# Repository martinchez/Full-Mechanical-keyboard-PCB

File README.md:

# Custom Mechanical Keyboard PCB Design

This repository contains the design files and resources for a custom mechanical keyboard PCB created using KiCad. The project includes schematics, PCB layout, and production files, aiming to make a fully functional and customizable mechanical keyboard.

## Project Overview

This keyboard design project includes:
- **Schematic Design**: Detailed layout of switches, diodes, and controller connections.
- **PCB Layout**: A compact and optimized PCB design suitable for mechanical switches.
- **Production Files**: Ready-to-use Gerber files and a BOM (Bill of Materials) for ordering components.

## Features

- **Hot-swappable Switches** (optional): Easy switch customization without soldering.
- **RGB Backlighting** (optional): Support for individually addressable RGB LEDs.
- **USB-C Interface**: Modern connectivity option.
- **Customizable Firmware**: Compatible with QMK or VIA for programmable key layouts.

## Folder Structure

- `schematics/`: KiCad schematic files for the keyboard circuit.
- `pcb_layout/`: KiCad PCB layout files with switch, diode, and microcontroller placements.
- `gerber_files/`: Gerber files for PCB manufacturing.
- `bom/`: Bill of Materials for sourcing components.

## Getting Started

1. Clone the repository:
   ```bash
   git clone 
   cd 
Open the project in KiCad by loading the .kicad_pro file in the root directory.

Make any modifications needed to suit your preferred keyboard layout.

## Usage
Editing the Schematic
Open the `schematics/` folder and modify connections or components as needed.

# PCB Layout
The `pcb_layout/` folder contains the PCB layout file, where you can make adjustments to the component placements or routing.

# Generating Gerber Files
After making changes, you can generate new Gerber files by:

1. Opening the PCB Editor in KiCad.
2. Going to File > Plot to export your Gerber files into the `gerber_files/` folder.

## License
This project is licensed under the MIT License

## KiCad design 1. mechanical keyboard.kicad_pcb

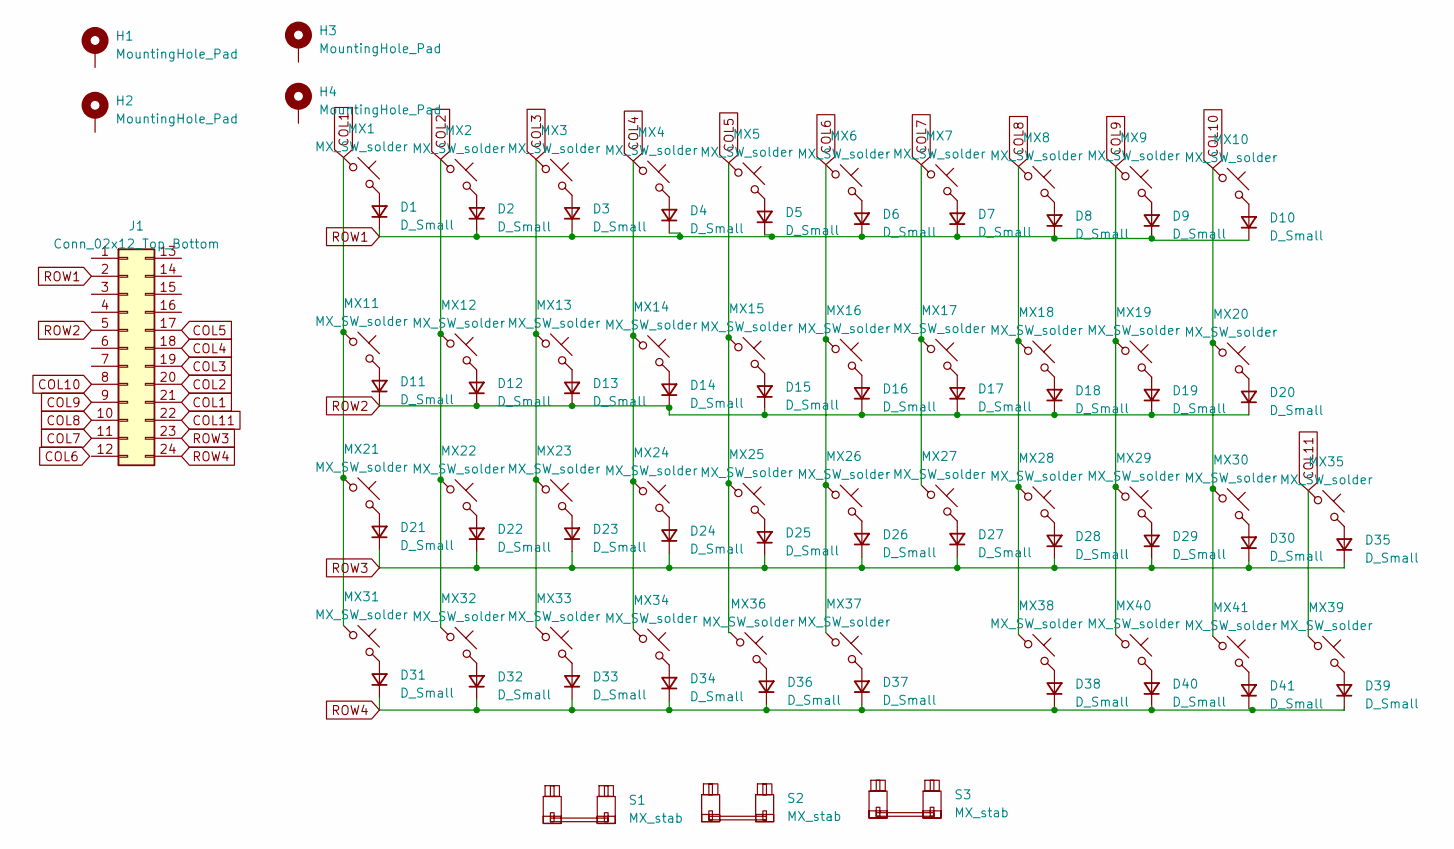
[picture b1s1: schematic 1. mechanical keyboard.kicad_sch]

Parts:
D1, D2, D3, D4, D5, D6, D7, D8, D9, D10, D11, D12, D13, D14, D15, D16, D17, D18, D19, D20, D21, D22, D23, D24, D25, D26, D27, D28, D29, D30, D31, D32, D33, D34, D35, D36, D37, D38, D39, D40, D41: D_Small; D_SOD-123
H1, H2, H3, H4: MountingHole_Pad; MountingHole_2.7mm_M2.5_Pad_Via
J1: Conn_02x12_Top_Bottom; ProMicro_Reversible_Single
MX1, MX2, MX3, MX4, MX5, MX6, MX7, MX8, MX9, MX12, MX13, MX14, MX15, MX16, MX17, MX18, MX19, MX22, MX23, MX24, MX25, MX26, MX27, MX28, MX29, MX30, MX32, MX33, MX34, MX35, MX36, MX37, MX38, MX39, MX40: MX_SW_solder; SW_MX_1u
MX10, MX21: MX_SW_solder; SW_MX_1.75u
MX11, MX31, MX41: MX_SW_solder; SW_MX_1.25u
MX20: MX_SW_solder; SW_MX_1.5u
S1: MX_stab; STAB_MX_P_2u
S2: MX_stab; STAB_MX_P_2.25u
S3: MX_stab; STAB_MX_P_6.25u

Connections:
COL1: J1.21, MX1.1, MX11.1, MX21.1, MX31.1
COL2: J1.20, MX2.1, MX12.1, MX22.1, MX32.1
COL3: J1.19, MX3.1, MX13.1, MX23.1, MX33.1
COL4: J1.18, MX4.1, MX14.1, MX24.1, MX34.1
COL5: J1.17, MX5.1, MX15.1, MX25.1, MX36.1
COL6: MX6.1, MX16.1, MX26.1, MX37.1
COL7: J1.11, MX7.1, MX17.1, MX27.1
COL8: J1.10, MX8.1, MX18.1, MX28.1, MX38.1
COL9: J1.9, MX9.1, MX19.1, MX29.1, MX40.1
COL10: J1.8, MX10.1, MX20.1, MX30.1, MX41.1
COL11: J1.22, MX35.1, MX39.1
unnamed: D1.2 (A), MX1.2
unnamed: D2.2 (A), MX2.2
unnamed: D3.2 (A), MX3.2
unnamed: D4.2 (A), MX4.2
unnamed: D5.2 (A), MX5.2
unnamed: D6.2 (A), MX6.2
unnamed: D7.2 (A), MX7.2
unnamed: D8.2 (A), MX8.2
unnamed: D9.2 (A), MX9.2
unnamed: D10.2 (A), MX10.2
unnamed: D11.2 (A), MX11.2
unnamed: D12.2 (A), MX12.2
unnamed: D13.2 (A), MX13.2
unnamed: D14.2 (A), MX14.2
unnamed: D15.2 (A), MX15.2
unnamed: D16.2 (A), MX16.2
unnamed: D17.2 (A), MX17.2
unnamed: D18.2 (A), MX18.2
unnamed: D19.2 (A), MX19.2
unnamed: D20.2 (A), MX20.2
unnamed: D21.2 (A), MX21.2
unnamed: D22.2 (A), MX22.2
unnamed: D23.2 (A), MX23.2
unnamed: D24.2 (A), MX24.2
unnamed: D25.2 (A), MX25.2
unnamed: D26.2 (A), MX26.2
unnamed: D27.2 (A), MX27.2
unnamed: D28.2 (A), MX28.2
unnamed: D29.2 (A), MX29.2
unnamed: D30.2 (A), MX30.2
unnamed: D31.2 (A), MX31.2
unnamed: D32.2 (A), MX32.2
unnamed: D33.2 (A), MX33.2
unnamed: D34.2 (A), MX34.2
unnamed: D35.2 (A), MX35.2
unnamed: D36.2 (A), MX36.2
unnamed: D37.2 (A), MX37.2
unnamed: D38.2 (A), MX38.2
unnamed: D39.2 (A), MX39.2
unnamed: D40.2 (A), MX40.2
unnamed: D41.2 (A), MX41.2
ROW1: D1.1 (K), D2.1 (K), D3.1 (K), D4.1 (K), D5.1 (K), D6.1 (K), D7.1 (K), D8.1 (K), D9.1 (K), D10.1 (K), J1.2
ROW2: D11.1 (K), D12.1 (K), D13.1 (K), D14.1 (K), D15.1 (K), D16.1 (K), D17.1 (K), D18.1 (K), D19.1 (K), D20.1 (K), J1.5
ROW3: D21.1 (K), D22.1 (K), D23.1 (K), D24.1 (K), D25.1 (K), D26.1 (K), D27.1 (K), D28.1 (K), D29.1 (K), D30.1 (K), D35.1 (K), J1.23
ROW4: D31.1 (K), D32.1 (K), D33.1 (K), D34.1 (K), D36.1 (K), D37.1 (K), D38.1 (K), D39.1 (K), D40.1 (K), D41.1 (K), J1.24

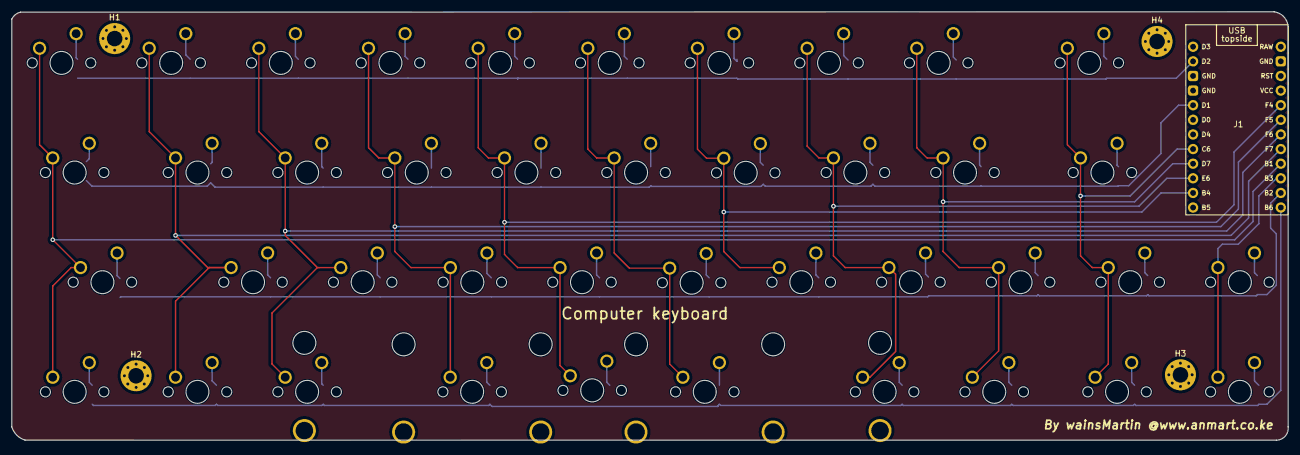
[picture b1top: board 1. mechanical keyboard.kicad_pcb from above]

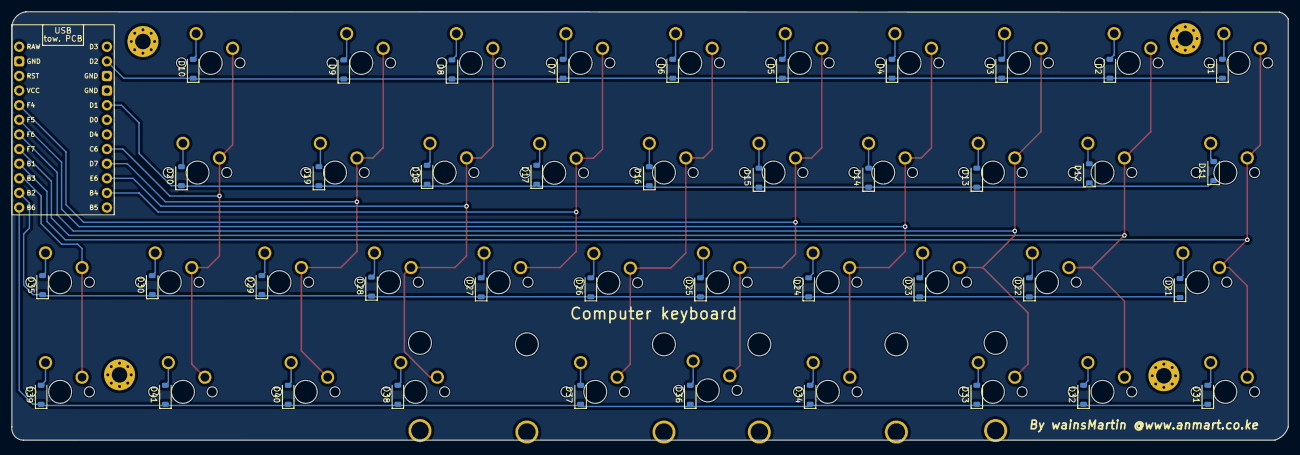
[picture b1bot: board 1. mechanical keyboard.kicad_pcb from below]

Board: 2 copper layers, 221.8 x 74.4 mm, 90 parts (41 on the bottom side), 56 nets.

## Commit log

2024-11-11 Readme
